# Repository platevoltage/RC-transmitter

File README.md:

MAKE_PIN(P0, 0);   // General I/O pin, mapped to GPIO21
MAKE_PIN(P1, 1);    // TX0, typically GPIO1 for UART0 TX
MAKE_PIN(P10, 10);  // TX1, mapped to GPIO17 for UART1 TX
MAKE_PIN(P3, 3);    // RX0, typically GPIO3 for UART0 RX
MAKE_PIN(P21, 21);   // SDA, typically GPIO8 for I2C SDA
MAKE_PIN(P22, 22);   // SCL, typically GPIO9 for I2C SCL
MAKE_PIN(P19, 9);  // MISO, typically GPIO12 for SPI MISO
MAKE_PIN(P23, 11);  // MOSI, typically GPIO13 for SPI MOSI
MAKE_PIN(P18, 7);  // SCK, typically GPIO14 for SPI SCK
MAKE_PIN(P5, 12);   // SS, typically GPIO15 for SPI SS
MAKE_PIN(P17, 5);   // INT, using GPIO4 for interrupt

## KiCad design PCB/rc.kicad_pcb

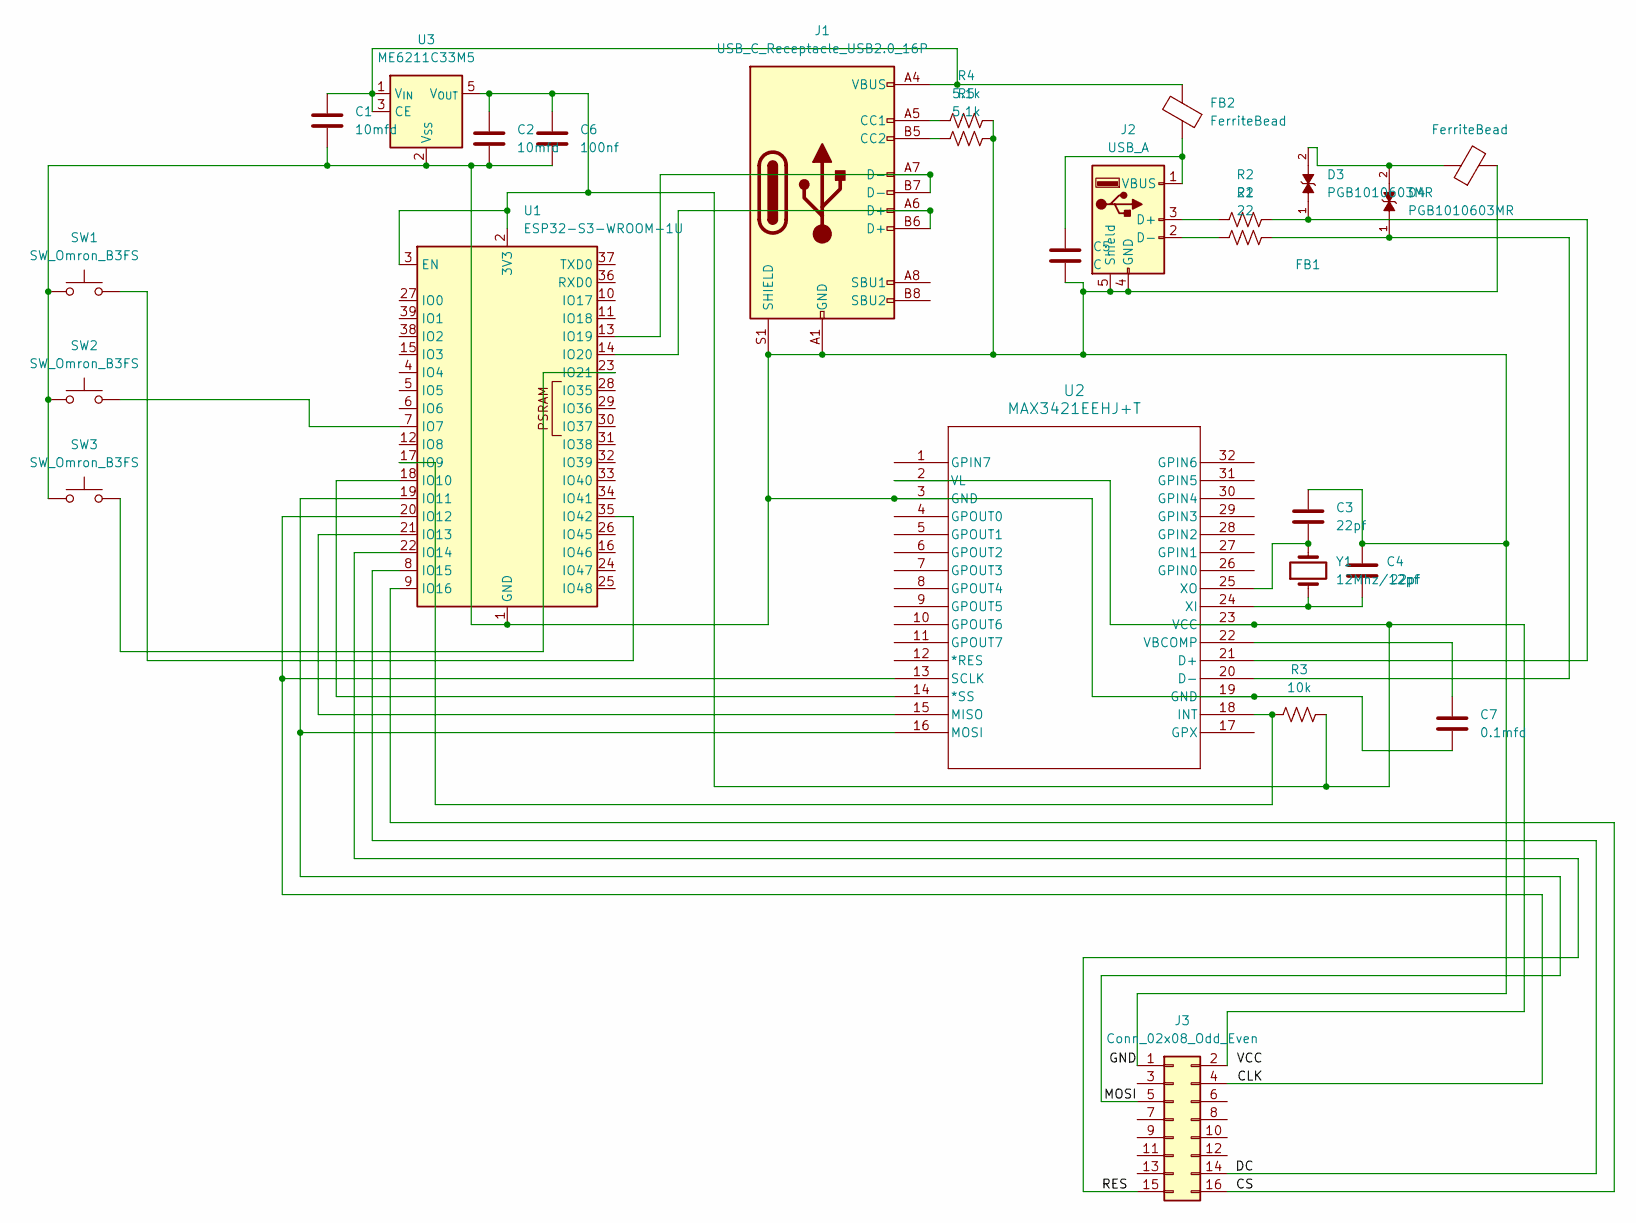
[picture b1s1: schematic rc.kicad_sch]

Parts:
C1, C2: 10mfd; C_0402_1005Metric_Pad0.74x0.62mm_HandSolder
C3, C4: 22pf; C_0402_1005Metric_Pad0.74x0.62mm_HandSolder
C5: C; C_0402_1005Metric_Pad0.74x0.62mm_HandSolder
C6: 100nf; C_0402_1005Metric_Pad0.74x0.62mm_HandSolder
C7: 0.1mfd; C_0402_1005Metric_Pad0.74x0.62mm_HandSolder
D3, D4: PGB1010603MR; DIOC1608X36N; PARTREV 07/27/15
FB1, FB2: FerriteBead; L_0603_1608Metric
J1: USB_C_Receptacle_USB2.0_16P; GCT_USB4120-03-C_REVA
J2: USB_A; ONSHORE_USB-A1VSB6
J3: Conn_02x08_Odd_Even; PinSocket_2x08_P2.54mm_Vertical
R1, R2: 22; R_0402_1005Metric_Pad0.72x0.64mm_HandSolder
R3: 10k; R_0402_1005Metric_Pad0.72x0.64mm_HandSolder
R4, R5: 5.1k; R_0402_1005Metric_Pad0.72x0.64mm_HandSolder
SW1, SW2, SW3: SW_Omron_B3FS; SW_SPST_Omron_B3FS-105xP
U1: ESP32-S3-WROOM-1U
U2: MAX3421EEHJ+T; 21-0110-C_90-0149-32L_MXM
U3: ME6211C33M5; SOT-23-5
Y1: 12Mhz/12pf; Crystal_SMD_G8-2Pin_3.2x1.5mm

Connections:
/CLK: J3.4, U1.20 (IO12), U2.13 (SCLK)
/CS: J3.16, U1.9 (IO16)
/DC: J3.14, U1.8 (IO15)
/GND: C1.2, C2.2, C3.1, C4.1, C5.2, C6.2, C7.2, FB1.2, J1.A1 (GND), J1.A12 (GND), J1.B1 (GND), J1.B12 (GND), J1.S1 (SHIELD), J2.4 (GND), J2.5 (Shield), J3.1, R4.2, R5.2, SW1.1, SW2.1, SW3.1, U1.1 (GND), U1.40 (GND), U1.41 (GND), U2.3 (GND), U2.19 (GND), U3.2 (V_{SS})
/MOSI: J3.5, U1.19 (IO11), U2.16 (MOSI)
/RES: J3.15, U1.22 (IO14)
unnamed: D3.2, D4.2, FB1.1
unnamed: J1.A5 (CC1), R4.1
unnamed: J1.B5 (CC2), R5.1
unnamed: J2.3 (D+), R2.1
unnamed: J2.2 (D-), R1.1
unnamed: C5.1, FB2.1, J2.1 (VBUS)
unnamed: C2.1, C6.1, J3.2, R3.2, U1.2 (3V3), U1.3 (EN), U2.2 (VL), U2.23 (VCC), U3.5 (V_{OUT})
unnamed: SW2.2, U1.7 (IO7)
unnamed: R3.1, U1.17 (IO9), U2.18 (INT)
unnamed: U1.18 (IO10), U2.14 (*SS)
unnamed: U1.21 (IO13), U2.15 (MISO)
unnamed: J1.A7 (D-), J1.B7 (D-), U1.13 (IO19)
unnamed: J1.A6 (D+), J1.B6 (D+), U1.14 (IO20)
unnamed: SW3.2, U1.23 (IO21)
unnamed: SW1.2, U1.35 (IO42)
unnamed: D3.1, R2.2, U2.21 (D+)
unnamed: D4.1, R1.2, U2.20 (D-)
unnamed: C7.1, U2.22 (VBCOMP)
unnamed: C4.2, U2.24 (XI), Y1.1
unnamed: C3.2, U2.25 (XO), Y1.2
unnamed: C1.1, FB2.2, J1.A4 (VBUS), J1.A9 (VBUS), J1.B4 (VBUS), J1.B9 (VBUS), U3.1 (V_{IN}), U3.3 (CE)

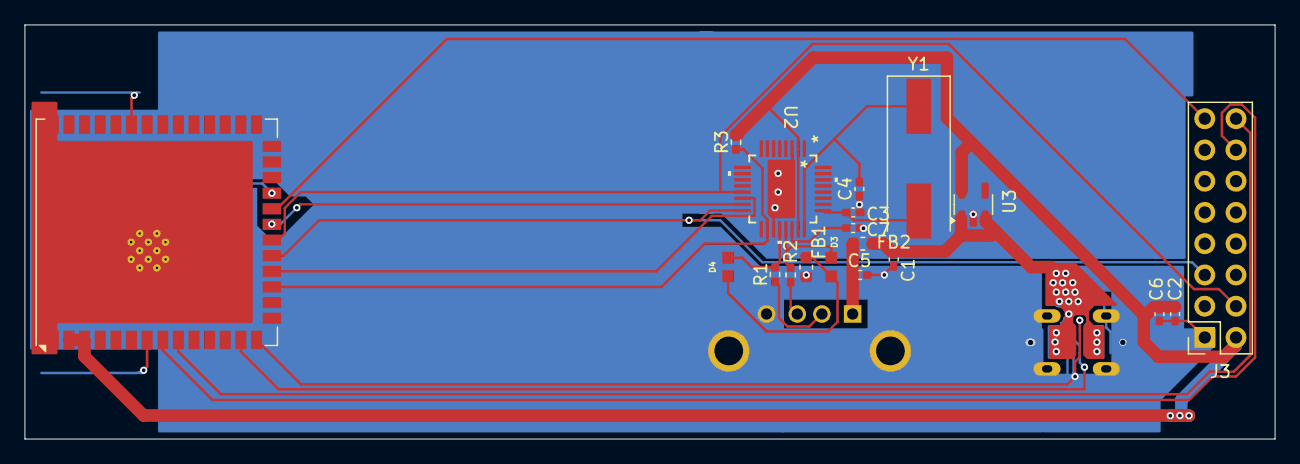
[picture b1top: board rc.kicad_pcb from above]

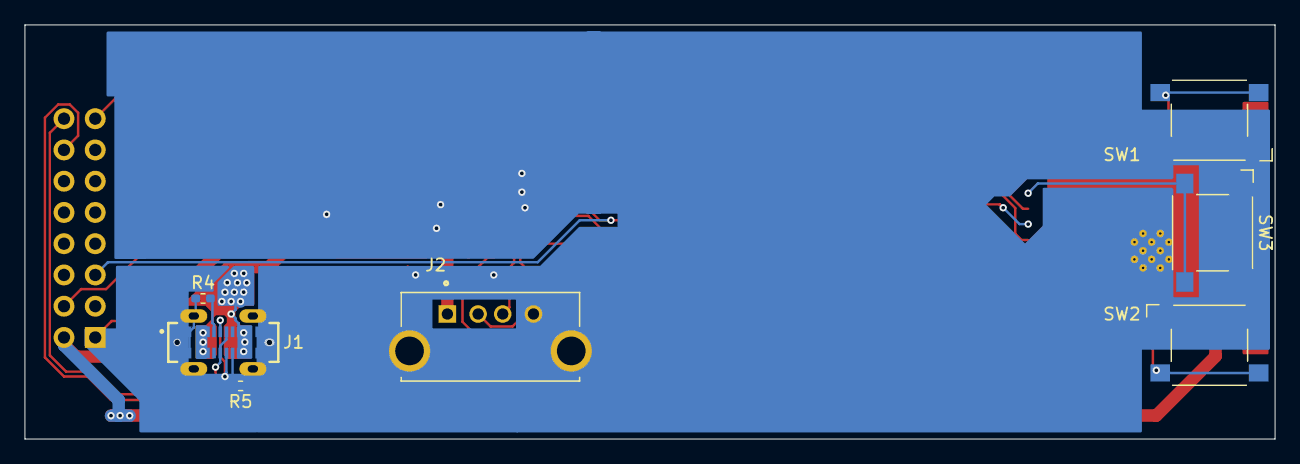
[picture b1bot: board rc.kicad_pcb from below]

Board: 2 copper layers, 101.6 x 33.7 mm, 26 parts (7 on the bottom side), 27 nets.

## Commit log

2024-07-04 init
2024-07-04 test
2024-07-04 moved more functions
2024-07-05 class
2024-07-05 renamed class
2024-07-05 custom USB host shield
2024-07-05 pass transmitter to parser
2024-07-06 stopping point
2024-07-06 getter
2024-07-07 bugs
2024-07-10 oled screen
2024-07-10 mapped dpad and abxy
2024-07-10 parsed reverse button
2024-07-10 start button
2024-07-11 reverse
2024-07-19 pcb init
2024-07-25 pcb update
2024-07-26 changed display constructor
2024-07-31 3 inch display
2024-08-02 more board
